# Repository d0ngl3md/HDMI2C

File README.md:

# HDMI2C
My adventure into I2C devices over HDMI
after running set up script, you are in i2c group, but .. theres a glitchy thing, might need need to log out and back in, though you are now member to the i2c group. as a member to the i2c group, with group ownership over the i2c devices, you should not need root to run programs accessing the i2c bus. thats the thought anyway. 

STEMMA 4-Pin I2C (both standard & STEMMA QT) <br>
<br>Black for GND. 
<br>Red for V+ 
<br>Blue for SDA. 
<br>Yellow for SCL

<br>
I just obsurved a singular device with several addresses, might try to write that into a serach option.
<br>
LCD 16x4, i2c base addresses, 0x20 thru 0x27
<br><br>
I had been messing with this on a display port to HDMI addapter, and could not get it to work.
When I switched over to a straight throught HDMI, it worked instantly!
<br>
sudo apt-install python3-dev
pip install smbus2

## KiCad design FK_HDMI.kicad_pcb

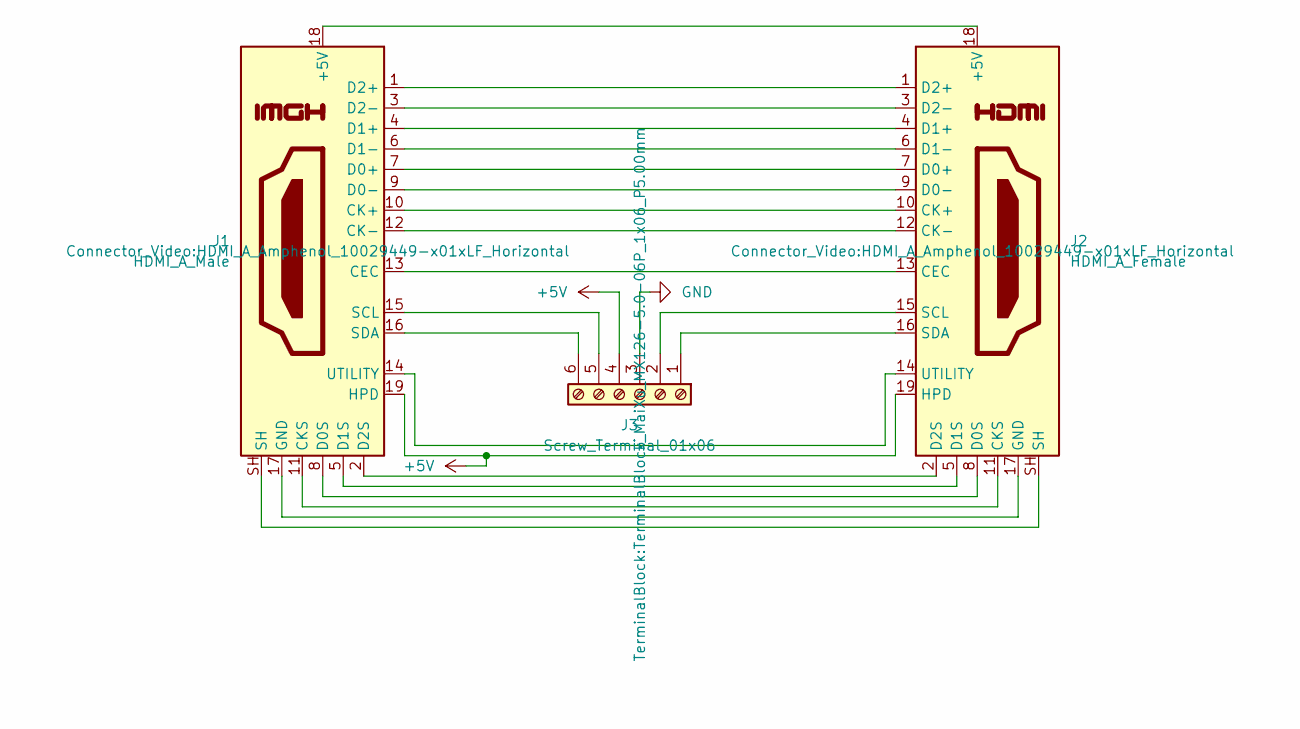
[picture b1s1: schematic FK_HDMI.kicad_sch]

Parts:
J1: HDMI_A_Male; HDMI_A_Amphenol_10029449-x01xLF_Horizontal
J2: HDMI_A_Female; HDMI_A_Amphenol_10029449-x01xLF_Horizontal
J3: Screw_Terminal_01x06; TerminalBlock_MaiXu_MX126-5.0-06P_1x06_P5.00mm

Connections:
+5V: J1.19 (HPD), J2.19 (HPD), J3.4
GND: J3.3
unnamed: J1.18 (+5V), J2.18 (+5V)
unnamed: J1.13 (CEC), J2.13 (CEC)
unnamed: J1.10 (CK+), J2.10 (CK+)
unnamed: J1.12 (CK-), J2.12 (CK-)
unnamed: J1.11 (CKS), J2.11 (CKS)
unnamed: J1.7 (D0+), J2.7 (D0+)
unnamed: J1.9 (D0-), J2.9 (D0-)
unnamed: J1.8 (D0S), J2.8 (D0S)
unnamed: J1.4 (D1+), J2.4 (D1+)
unnamed: J1.6 (D1-), J2.6 (D1-)
unnamed: J1.5 (D1S), J2.5 (D1S)
unnamed: J1.1 (D2+), J2.1 (D2+)
unnamed: J1.3 (D2-), J2.3 (D2-)
unnamed: J1.2 (D2S), J2.2 (D2S)
unnamed: J1.17 (GND), J2.17 (GND)
unnamed: J1.SH, J2.SH
unnamed: J1.15 (SCL), J3.5
unnamed: J1.16 (SDA), J3.6
unnamed: J1.14 (UTILITY), J2.14 (UTILITY)
unnamed: J2.15 (SCL), J3.2
unnamed: J2.16 (SDA), J3.1

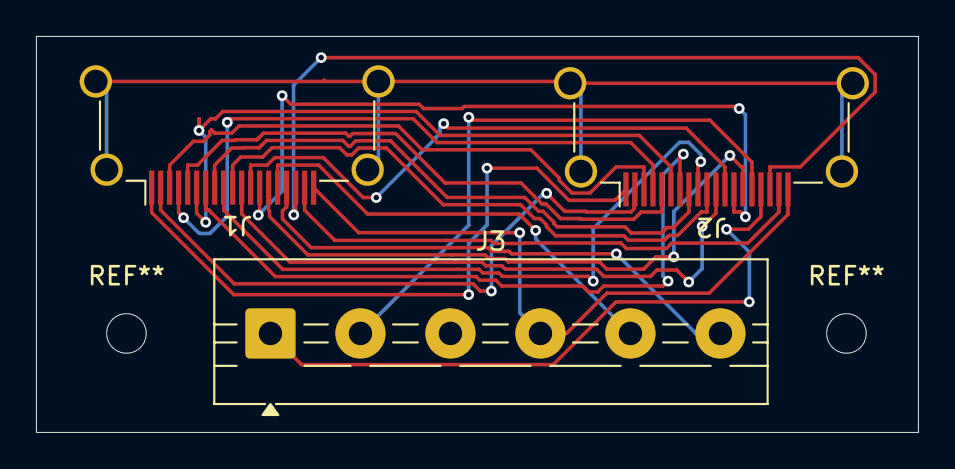
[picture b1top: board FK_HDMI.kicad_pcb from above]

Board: 2 copper layers, 49.0 x 22.0 mm, 3 parts (0 on the bottom side), 22 nets.

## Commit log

2025-03-03 Update findI2C_addr.sh
    -r for readonly mode
2025-03-29 kicad hdmi tap files
2025-03-30 Update findI2C_addr.sh
    no addr? scan all
2025-03-30 graceful error msg
2025-03-30 figured out how all this works now
2025-03-31 almost caused a future headache lol
2025-04-02 start a list of avialable hardware
2025-04-15 Add files via upload
    Did pcb design in kicad 9. Used plugins pcb way, and freerouter, also assigned footprints to schematic components.
